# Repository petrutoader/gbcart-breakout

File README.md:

# gbcart-breakout
Breakout board EAGLE schematics for the cartridge slot of the Game Boy (DMG/Color/GBA)

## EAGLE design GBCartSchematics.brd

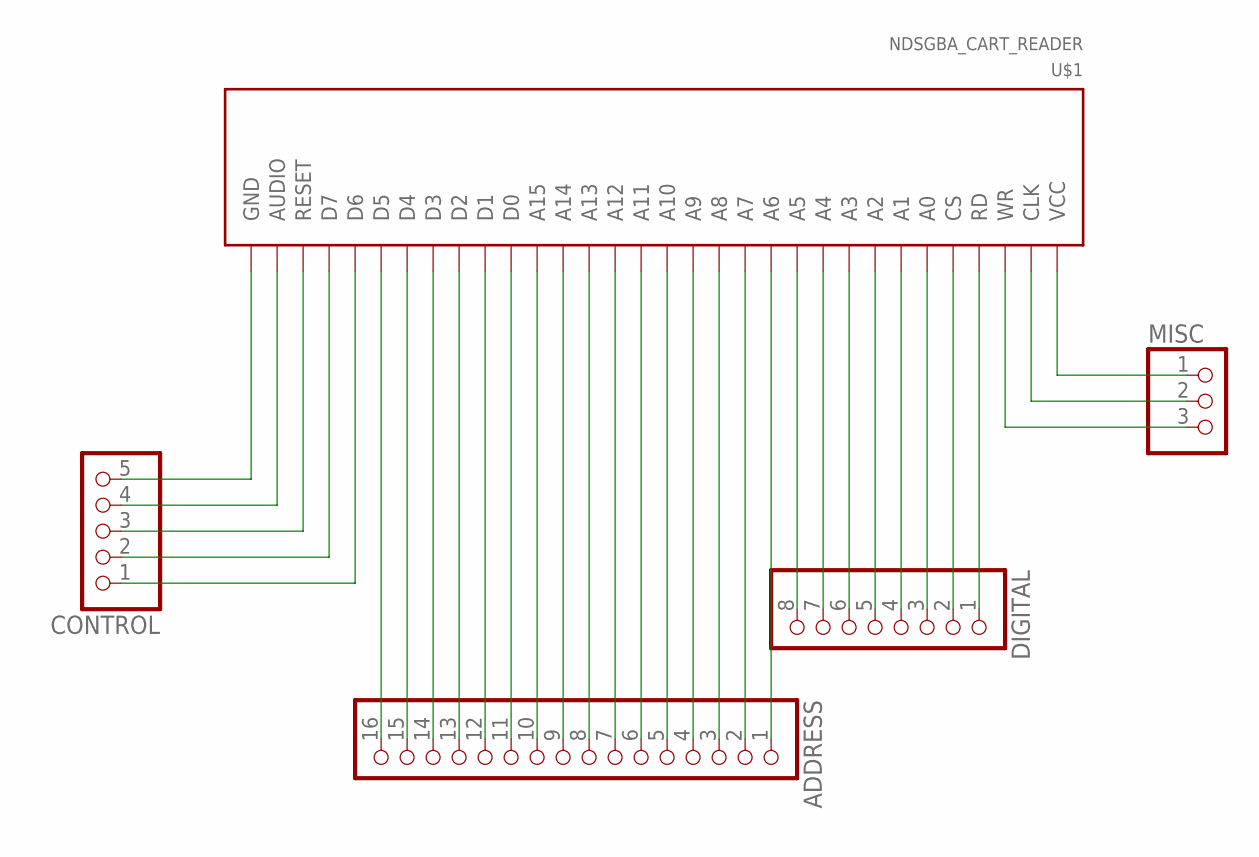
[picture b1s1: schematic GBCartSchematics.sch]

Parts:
ADDRESS: PINHD-1X16; 1X16
CONTROL: PINHD-1X5; 1X05
DIGITAL: PINHD-1X8; 1X08
MISC: PINHD-1X3; 1X03
U$1: NDSGBA_CART_READER

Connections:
A0: ADDRESS.16, U$1.27 (D5)
A1: ADDRESS.15, U$1.26 (D4)
A2: ADDRESS.14, U$1.25 (D3)
A3: ADDRESS.13, U$1.24 (D2)
A4: ADDRESS.12, U$1.23 (D1)
A5: ADDRESS.11, U$1.22 (D0)
A6: ADDRESS.10, U$1.21 (A15)
A7: ADDRESS.9, U$1.20 (A14)
A8: ADDRESS.8, U$1.19 (A13)
A9: ADDRESS.7, U$1.18 (A12)
A10: ADDRESS.6, U$1.17 (A11)
A11: ADDRESS.5, U$1.16 (A10)
A12: ADDRESS.4, U$1.15 (A9)
A13: ADDRESS.3, U$1.14 (A8)
A14: ADDRESS.2, U$1.13 (A7)
A15: ADDRESS.1, U$1.12 (A6)
AUDIO_IN: MISC.2, U$1.2 (CLK)
CLK: CONTROL.4, U$1.31 (AUDIO)
CS_SRAM: CONTROL.1, U$1.28 (D6)
D0: DIGITAL.8, U$1.11 (A5)
D1: DIGITAL.7, U$1.10 (A4)
D2: DIGITAL.6, U$1.9 (A3)
D3: DIGITAL.5, U$1.8 (A2)
D4: DIGITAL.4, U$1.7 (A1)
D5: DIGITAL.3, U$1.6 (A0)
D6: DIGITAL.2, U$1.5 (CS)
D7: DIGITAL.1, U$1.4 (RD)
GND: MISC.1, U$1.1 (VCC)
RD: CONTROL.2, U$1.29 (D7)
RESET: MISC.3, U$1.3 (WR)
VCC: CONTROL.5, U$1.32 (GND)
WR: CONTROL.3, U$1.30 (RESET)

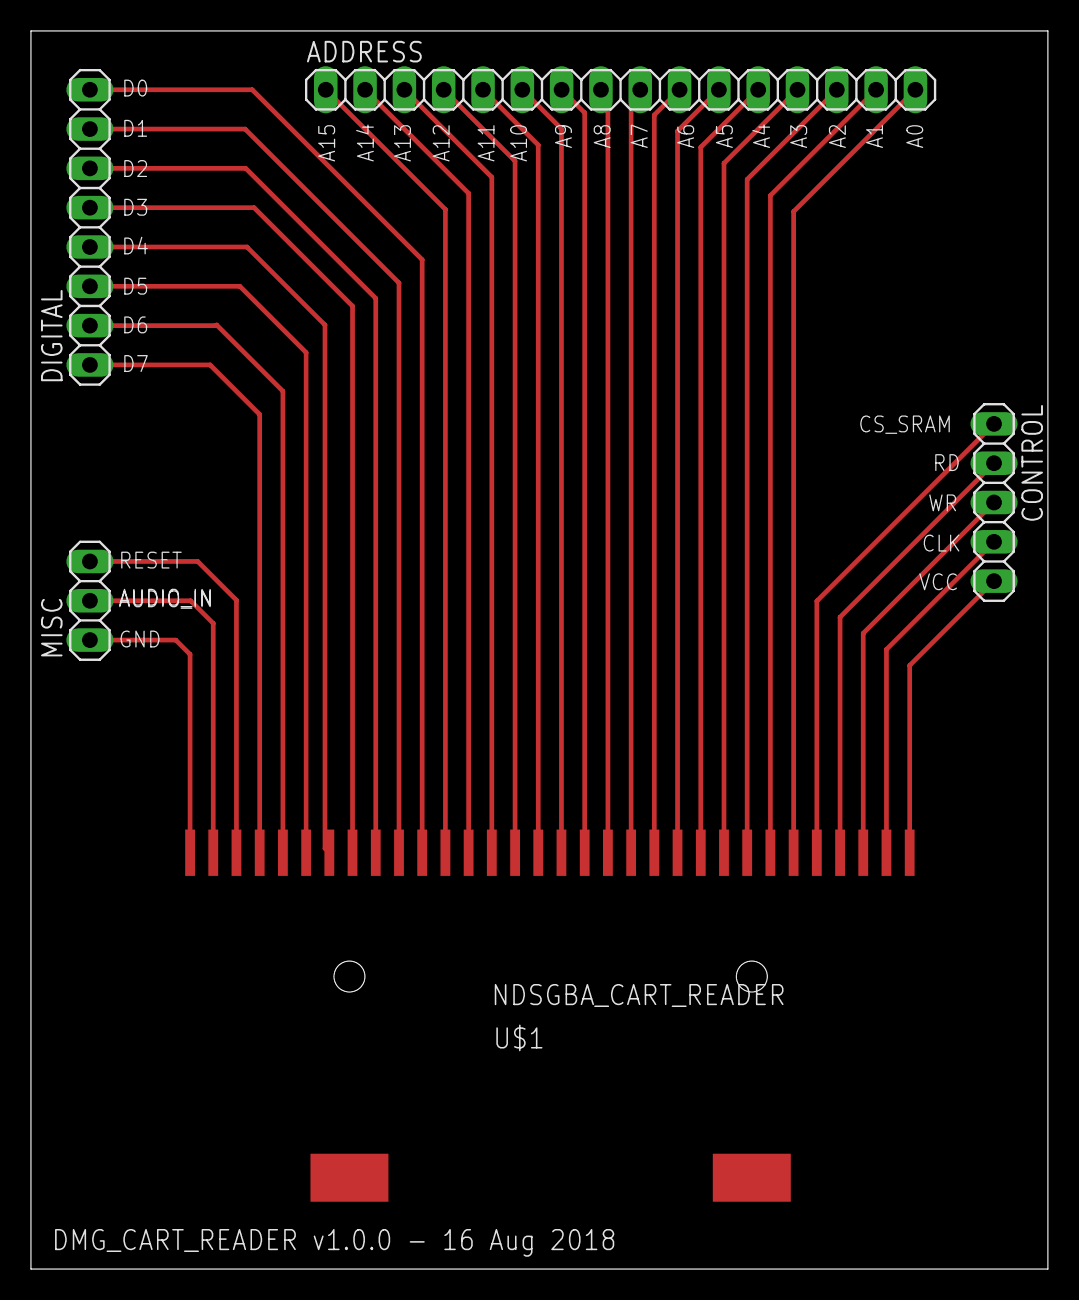
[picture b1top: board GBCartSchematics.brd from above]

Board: 2 copper layers, 65.7 x 80.0 mm, 5 parts (0 on the bottom side), 32 nets.

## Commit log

2018-09-20 Remove backup versions
2019-03-04 Improved wiring (omg, lol) and added gitignore, fixed text issues on addressing pins
2019-03-04 Nothing to brag about with that autorouting, removing from README as it's no longer up to date.
